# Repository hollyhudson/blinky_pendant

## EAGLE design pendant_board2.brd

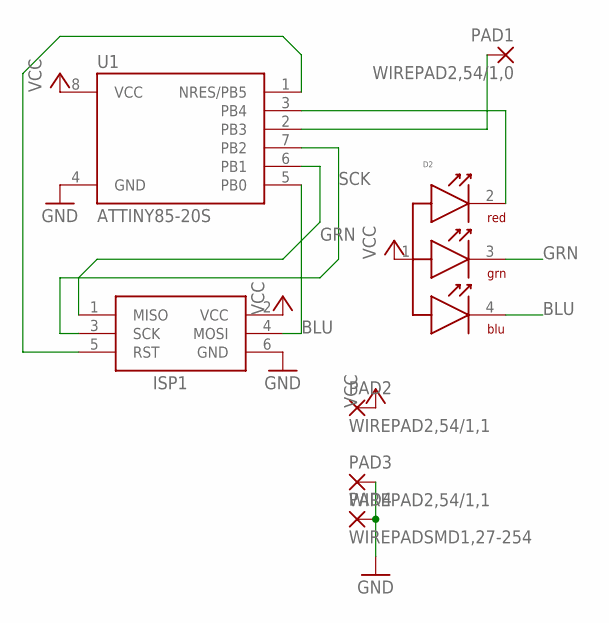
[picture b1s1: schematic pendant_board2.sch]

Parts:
D2: SM1210RGB
ISP1: AVRISP-BOX
PAD1: WIREPAD2,54/1,0; 2,54/1,0
PAD2, PAD3: WIREPAD2,54/1,1; 2,54/1,1
PAD4: WIREPADSMD1,27-254; SMD1,27-2,54
U1: ATTINY85-20S; SOIC8_EIAJ_208MIL

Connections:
BLU: D2.4 (BLU), ISP1.4 (MOSI), U1.5 (PB0)
GND: ISP1.6 (GND), PAD3.1, PAD4.1, U1.4 (GND)
GRN: D2.3 (GRN), ISP1.1 (MISO), U1.6 (PB1)
unnamed: D2.2 (RED), U1.3 (PB4)
unnamed: PAD1.1, U1.2 (PB3)
unnamed: ISP1.5 (RST), U1.1 (NRES/PB5)
SCK: ISP1.3 (SCK), U1.7 (PB2)
VCC: D2.1 (VCC), ISP1.2 (VCC), PAD2.1, U1.8 (VCC)

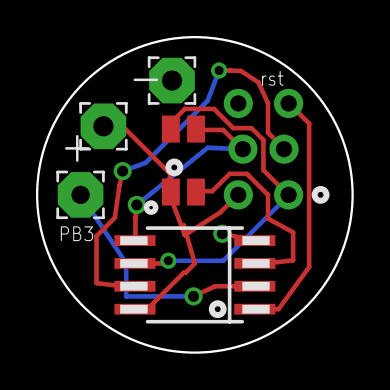
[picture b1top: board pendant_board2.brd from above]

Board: 2 copper layers, 17.5 x 17.5 mm, 7 parts (1 on the bottom side), 8 nets.

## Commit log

2014-04-05 inital add of all this stuff
2014-04-05 Added firmware for the pendant. RGB blinktest.
2014-04-06 Added an empty README.md
